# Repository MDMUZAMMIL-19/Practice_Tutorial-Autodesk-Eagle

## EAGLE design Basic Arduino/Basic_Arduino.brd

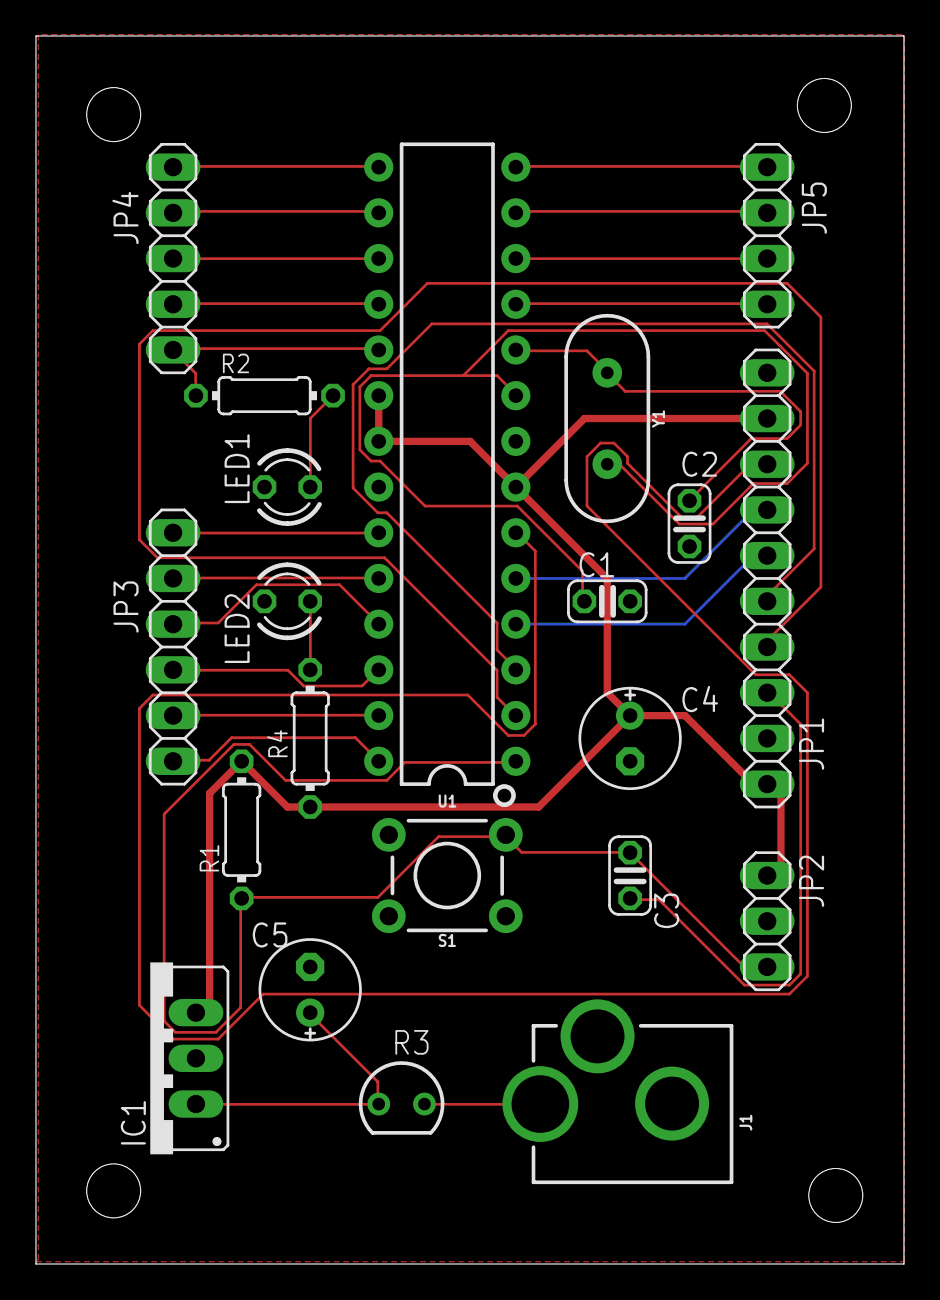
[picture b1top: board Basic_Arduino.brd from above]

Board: 2 copper layers, 48.2 x 68.2 mm, 21 parts (0 on the bottom side), 30 nets.

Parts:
C1, C2: 22pF; C025-024X044
C3: 0.1uF; C025-024X044
C4, C5: 10uF; E2,5-6E
IC1: 78XXS
J1: POWER_JACKPTH_LOCK; POWER_JACK_PTH_LOCK
JP1: 1X10
JP2: 1X03
JP3: 1X06
JP4: 1X05
JP5: 1X04
LED1, LED2: LED3MM
R1: 10K; 0204/7
R2, R4: 220E; 0204/7
R3: PTC-SOD70; SOD70
S1: SPST; TACTILE_SWITCH_PTH_6.0MM
U1: 328P; DIP28
Y1: 16MHz; HC49US

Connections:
!RESET: C3.1, JP2.3, R1.1, S1.3, U1.1
A0: JP3.1, U1.23
A1: JP3.2, U1.24
A2: JP3.3, U1.25
A3: JP3.4, U1.26
A4: JP3.5, U1.27
A5: JP3.6, U1.28
D2: JP1.6, U1.4
D3: JP1.7, U1.5
D4: JP1.8, U1.6
D5: JP5.1, U1.11
D6: JP5.2, U1.12
D7: JP5.3, U1.13
D8: JP5.4, U1.14
D9: JP4.1, U1.15
D10: JP4.2, U1.16
D11: JP4.3, U1.17
D12: JP4.4, U1.18
D13: JP4.5, R2.1, U1.19
DTR: C3.2, JP1.3
GND: C1.2, C2.2, C4.-, C5.-, IC1.GND, J1.GND, J1.GNDBREAK, JP1.2, JP1.10, JP2.2, LED1.K, LED2.K, S1.1, U1.8, U1.22
unnamed: C1.1, U1.9, Y1.2
unnamed: J1.PWR, R3.2
unnamed: LED2.A, R4.2
unnamed: C5.+, IC1.IN, R3.1
unnamed: C2.1, U1.10, Y1.1
unnamed: LED1.A, R2.2
RX: JP1.4, U1.2
TX: JP1.5, U1.3
VCC: C4.+, IC1.OUT, JP1.1, JP1.9, JP2.1, R1.2, R4.1, U1.7, U1.20, U1.21

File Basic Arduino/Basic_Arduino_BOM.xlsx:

Qty | Value | Device | Package | Parts | Description
1 |  | 78XXS | 78XXS | IC1 | VOLTAGE REGULATOR
2 |  | LED3MM | LED3MM | LED1, LED2 | LED
1 |  | PINHD-1X10 | 1X10 | JP1 | PIN HEADER
1 |  | PINHD-1X3 | 1X03 | JP2 | PIN HEADER
1 |  | PINHD-1X4 | 1X04 | JP5 | PIN HEADER
1 |  | PINHD-1X5 | 1X05 | JP4 | PIN HEADER
1 |  | PINHD-1X6 | 1X06 | JP3 | PIN HEADER
1 | 0.1uF | C-US025-024X044 | C025-024X044 | C3 | CAPACITOR, American symbol
1 | 10K | R-US_0204/7 | 0204/7 | R1 | RESISTOR, American symbol
2 | 10uF | CPOL-USE2,5-6E | E2,5-6E | C4, C5 | POLARIZED CAPACITOR, American symbol
1 | 16MHz | CRYSTAL-16MHZPTH-HC49US | HC49US | Y1 | 16MHz Crystal
2 | 220E | R-US_0204/7 | 0204/7 | R2, R4 | RESISTOR, American symbol
2 | 22pF | C-US025-024X044 | C025-024X044 | C1, C2 | CAPACITOR, American symbol
1 | 328P | ATMEGA328P_PDIP | DIP28 | U1 | Atmel 328P
1 | POWER_JACKPTH_LOCK | POWER_JACKPTH_LOCK | POWER_JACK_PTH_LOCK | J1 | Power Jack Connector
1 | PTC-SOD70 | PTC-SOD70 | SOD70 | R3 | Positive Temperature Coefficient Resistor (PTC) termistor
1 | SPST | MOMENTARY-SWITCH-SPST-PTH-6.0MM | TACTILE_SWITCH_PTH_6.0MM | S1 | Momentary Switch (Pushbutton) - SPST

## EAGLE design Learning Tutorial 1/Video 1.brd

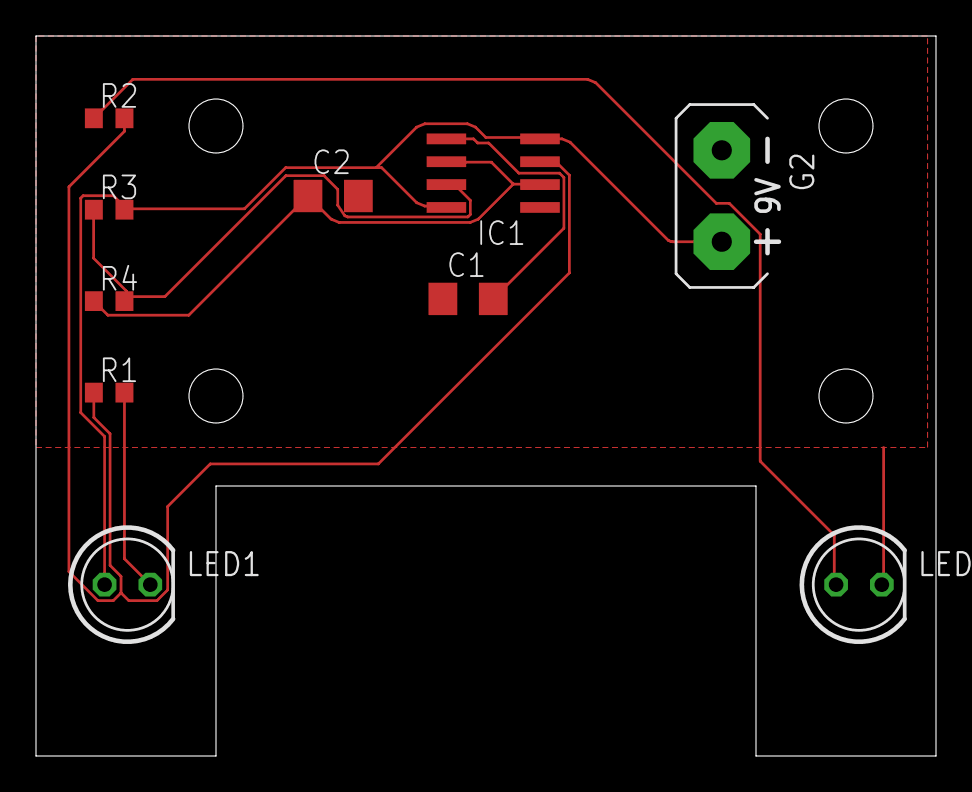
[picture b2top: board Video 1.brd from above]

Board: 2 copper layers, 50.0 x 40.0 mm, 10 parts (0 on the bottom side), 8 nets.

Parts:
C1: 10nF; C1206
C2: 1nF; C1206
G2: AB9V
IC1: NE555D; SO08
LED1, LED2: LED5MM
R1: 330E; R0603
R2: 300E; R0603
R3: 1k; R0603
R4: 100k; R0603

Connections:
+9V: G2.+, IC1.4, IC1.8, LED1.A, R3.2
GND: C1.1, C2.2, G2.-, IC1.1, LED2.K
unnamed: C2.1, IC1.2, IC1.6, R4.1
unnamed: LED1.K, R1.2
unnamed: IC1.3, R1.1, R2.2
unnamed: LED2.A, R2.1
unnamed: IC1.7, R3.1, R4.2
unnamed: C1.2, IC1.5

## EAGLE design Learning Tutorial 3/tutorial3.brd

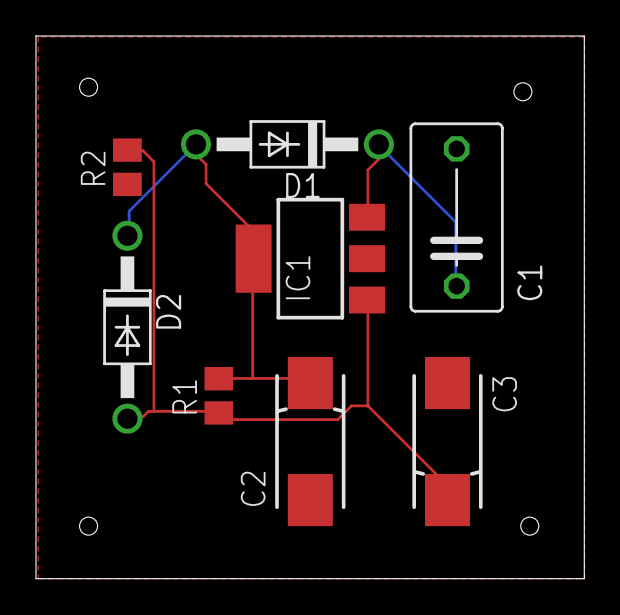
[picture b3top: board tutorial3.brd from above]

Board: 2 copper layers, 30.5 x 30.1 mm, 8 parts (0 on the bottom side), 4 nets.

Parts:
C1: 0.1uF; C075-052X106
C2: 1uF; 085CS_1AR
C3: 10uF; 085CS_1AR
D1, D2: 1N4002; DO41-10
IC1: LM317MBSTT3; SOT223
R1: 240Ω; M0805
R2: 720Ω; M0805

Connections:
GND: C1.2, C2.-, C3.-, R2.1
unnamed: C3.+, D2.A, IC1.1, R1.1, R2.2
VIN: C1.1, D1.C, IC1.3
VO: C2.+, D1.A, D2.C, IC1.4, R1.2

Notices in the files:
parts and their libraries:
SparkFun-Connectors: Licensing: Creative Commons ShareAlike 4.0 International - https://creativecommons.org/licenses/by-sa/4.0
